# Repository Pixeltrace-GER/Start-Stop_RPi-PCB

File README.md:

> __Warning__  <br>**WORK IN PROGRESS** <br>Please wait for a stable release or get in touch with me.

# Start & Stop HAT PCB

## Features Raspberry
-  Cooling Fan 2510
-  GCode Button ~~5x~~ 3x
-  GCode Button Led ~~5x~~ 3x
-  Relay Connector for 2x 10A 250VAC

## Features D1mini
-  Start & Stop relay [HF46F/5-HS1]
-  I2C SSD1306 OLED
-  Error LED [red 0805]
-  WiFi-AP Config
-  EEPROM saved Config

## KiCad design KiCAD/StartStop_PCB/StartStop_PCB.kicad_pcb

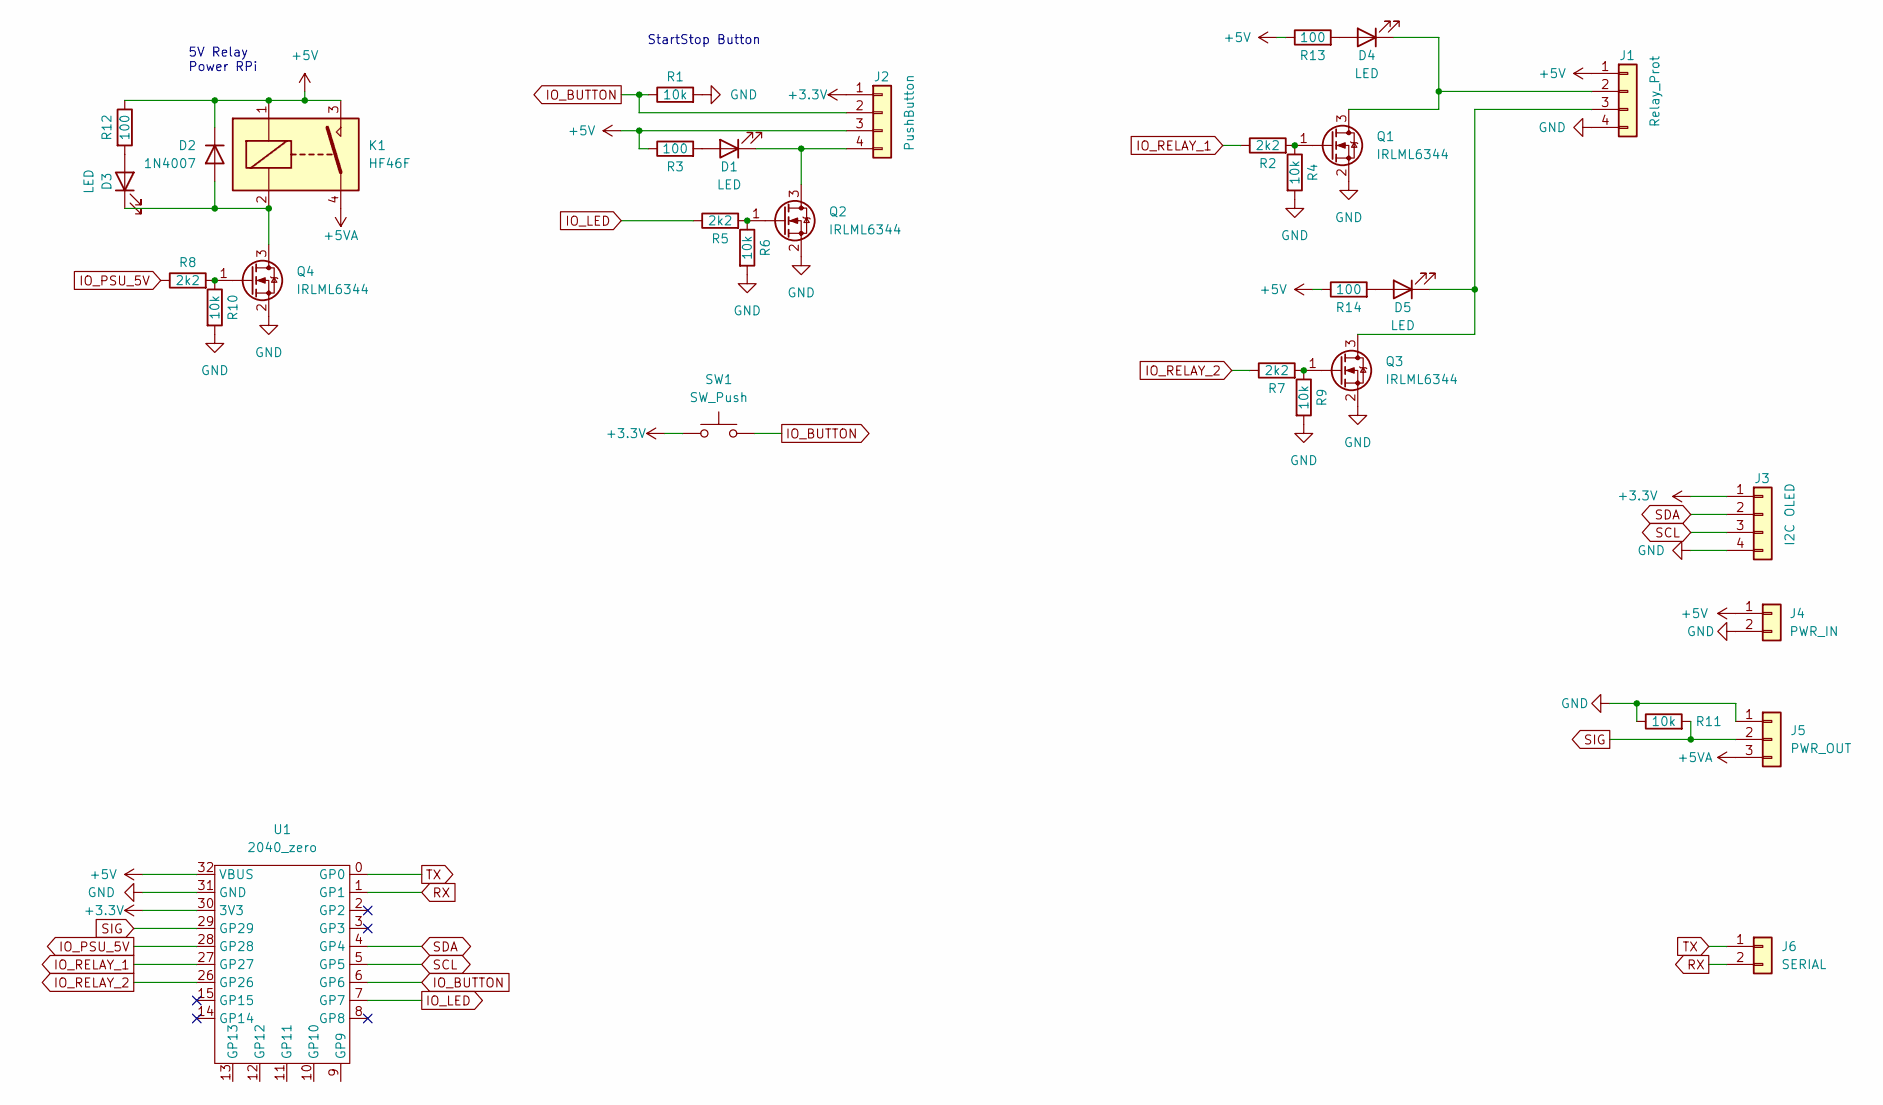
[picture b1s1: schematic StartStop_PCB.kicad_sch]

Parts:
D1, D3, D4, D5: LED; LED_0805_2012Metric
D2: 1N4007; D_SOD-123
J1: Relay_Prot; JST_XH_B4B-XH-A_1x04_P2.50mm_Vertical
J2: PushButton; JST_XH_B4B-XH-A_1x04_P2.50mm_Vertical
J3: I2C OLED; JST_XH_B4B-XH-A_1x04_P2.50mm_Vertical
J4: PWR_IN; Molex_Micro-Fit_3.0_43650-0215_1x02_P3.00mm_Vertical
J5: PWR_OUT; Molex_Micro-Fit_3.0_43650-0315_1x03_P3.00mm_Vertical
J6: SERIAL; JST_XH_B2B-XH-A_1x02_P2.50mm_Vertical
K1: HF46F
Q1, Q2, Q3, Q4: IRLML6344; SOT-23
R1, R4, R6, R9, R10, R11: 10k; R_0805_2012Metric
R2, R5, R7, R8: 2k2; R_0805_2012Metric
R3, R12, R13, R14: 100; R_0805_2012Metric
SW1: SW_Push; SW_04-03
U1: 2040_zero; rp2040_zero

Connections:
+3.3V: J2.1, J3.1, SW1.1, U1.30 (3V3)
+5V: D2.1 (K), J1.1, J2.3, J4.1, K1.1, K1.3, R3.1, R12.1, R13.1, R14.1, U1.32 (VBUS)
+5VA: J5.3, K1.4
GND: J1.4, J3.4, J4.2, J5.1, Q1.2 (S), Q2.2 (S), Q3.2 (S), Q4.2 (S), R1.2, R4.2, R6.2, R9.2, R10.2, R11.1, U1.31 (GND)
IO_BUTTON: J2.2, R1.1, SW1.2, U1.6 (GP6)
IO_LED: R5.1, U1.7 (GP7)
IO_PSU_5V: R8.1, U1.28 (GP28)
IO_RELAY_1: R2.1, U1.27 (GP27)
IO_RELAY_2: R7.1, U1.26 (GP26)
unnamed: D1.1 (K), J2.4, Q2.3 (D)
unnamed: D1.2 (A), R3.2
unnamed: D2.2 (A), D3.1 (K), K1.2, Q4.3 (D)
unnamed: D3.2 (A), R12.2
unnamed: D4.1 (K), J1.2, Q1.3 (D)
unnamed: D4.2 (A), R13.2
unnamed: D5.1 (K), J1.3, Q3.3 (D)
unnamed: D5.2 (A), R14.2
unnamed: Q1.1 (G), R2.2, R4.1
unnamed: Q2.1 (G), R5.2, R6.1
unnamed: Q3.1 (G), R7.2, R9.1
unnamed: Q4.1 (G), R8.2, R10.1
RX: J6.2, U1.1 (GP1)
SCL: J3.3, U1.5 (GP5)
SDA: J3.2, U1.4 (GP4)
SIG: J5.2, R11.2, U1.29 (GP29)
TX: J6.1, U1.0 (GP0)

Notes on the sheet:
5V Relay Power RPi
StartStop Button

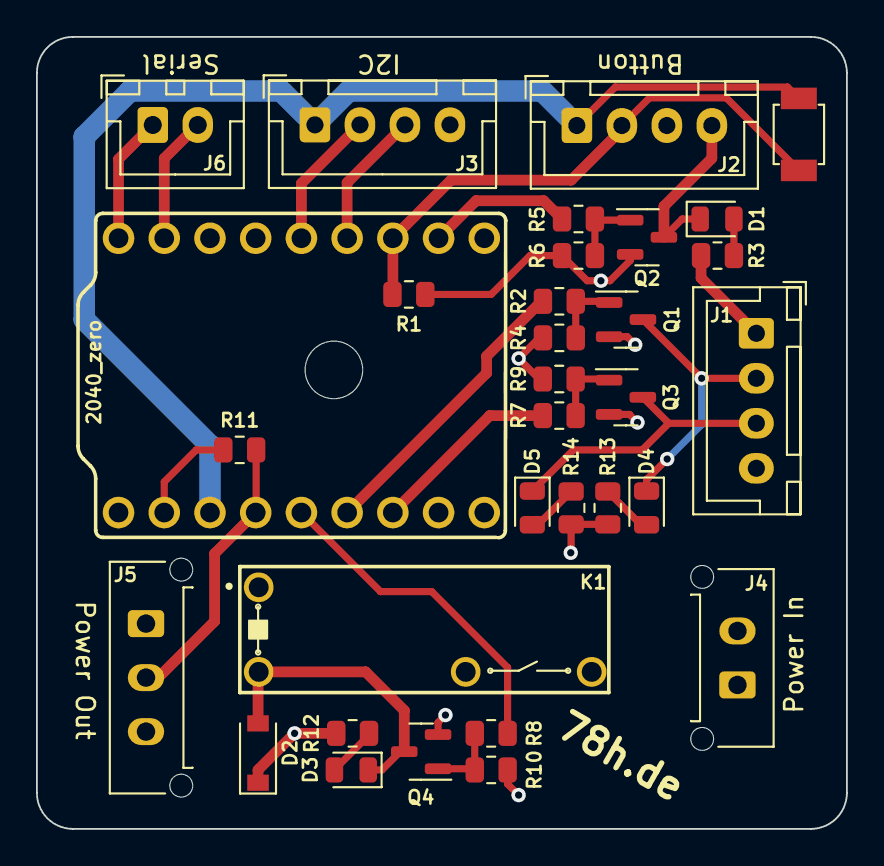
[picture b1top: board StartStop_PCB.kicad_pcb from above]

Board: 4 copper layers, 45.0 x 44.0 mm, 32 parts (0 on the bottom side), 26 nets.

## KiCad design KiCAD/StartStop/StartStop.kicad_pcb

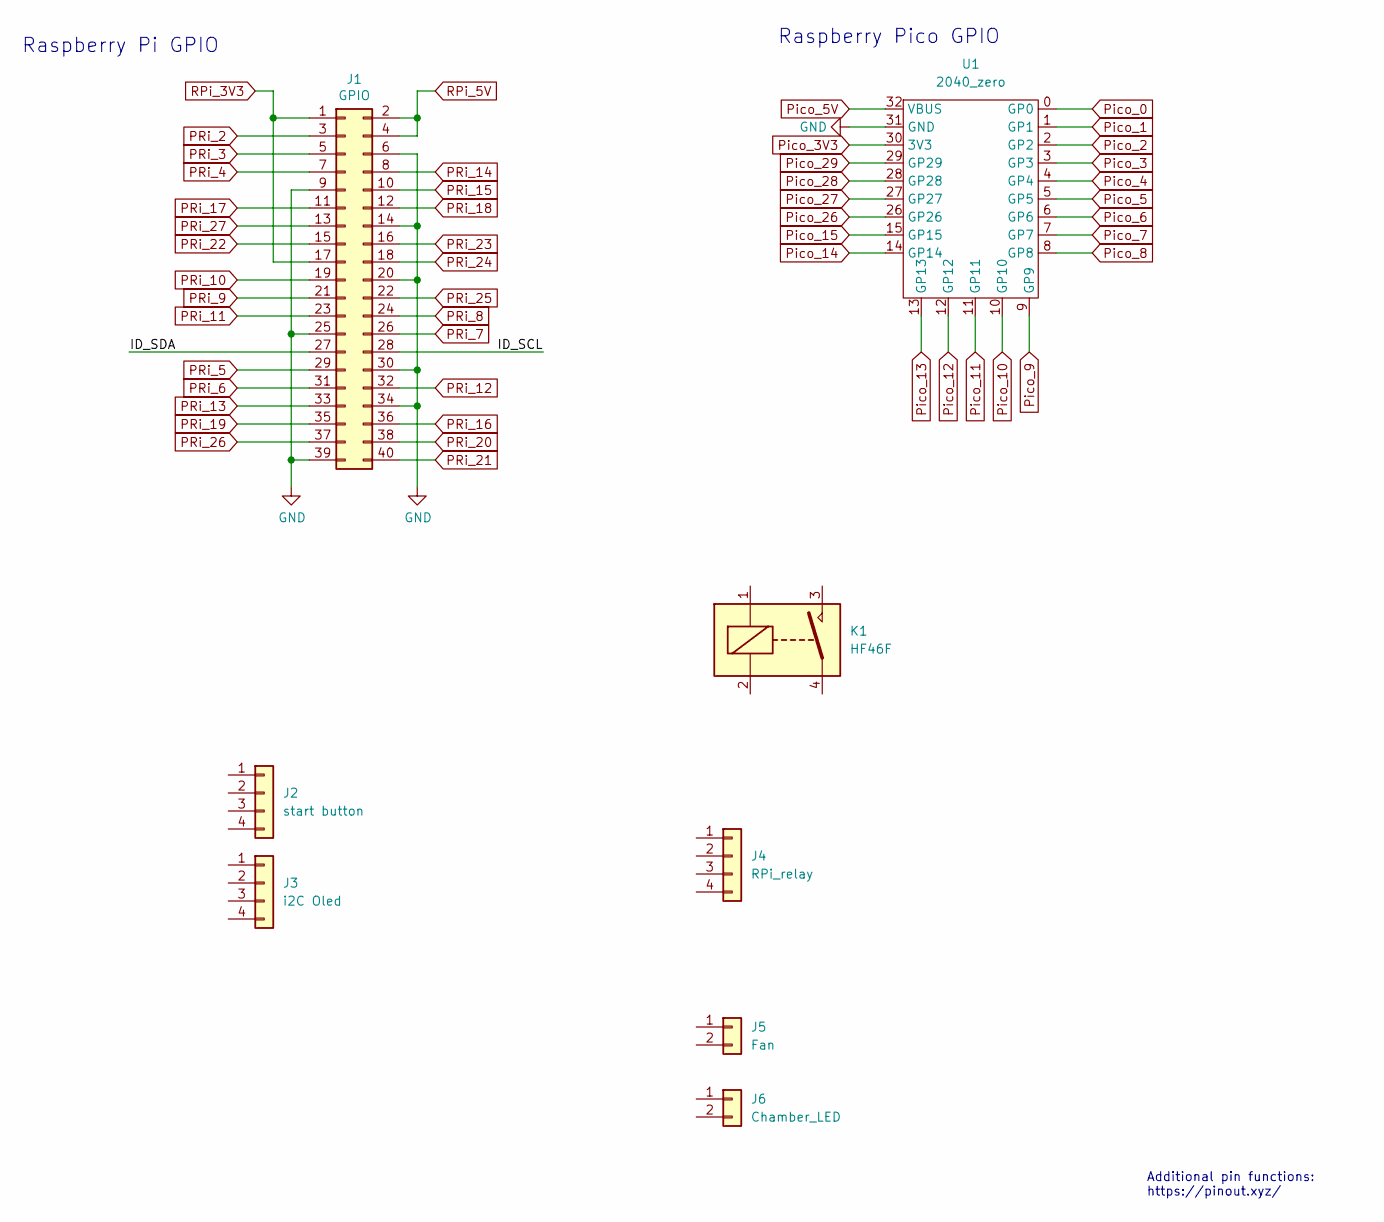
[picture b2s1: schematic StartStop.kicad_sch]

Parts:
J1: GPIO; PinSocket_2x20_P2.54mm_Vertical
J2: start button; JST_PH_B4B-PH-K_1x04_P2.00mm_Vertical
J3: i2C Oled; JST_PH_B4B-PH-K_1x04_P2.00mm_Vertical
J4: RPi_relay; JST_PH_B4B-PH-K_1x04_P2.00mm_Vertical
J5: Fan; JST_PH_B2B-PH-K_1x02_P2.00mm_Vertical
J6: Chamber_LED; JST_PH_B2B-PH-K_1x02_P2.00mm_Vertical
K1: HF46F
U1: 2040_zero; rp2040_zero

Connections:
/ID_SCL: J1.28
/ID_SDA: J1.27
GND: J1.6, J1.9, J1.14, J1.20, J1.25, J1.30, J1.34, J1.39, U1.31 (GND)
PRi_2: J1.3
PRi_3: J1.5
PRi_4: J1.7
PRi_5: J1.29
PRi_6: J1.31
PRi_7: J1.26
PRi_8: J1.24
PRi_9: J1.21
PRi_10: J1.19
PRi_11: J1.23
PRi_12: J1.32
PRi_13: J1.33
PRi_14: J1.8
PRi_15: J1.10
PRi_16: J1.36
PRi_17: J1.11
PRi_18: J1.12
PRi_19: J1.35
PRi_20: J1.38
PRi_21: J1.40
PRi_22: J1.15
PRi_23: J1.16
PRi_24: J1.18
PRi_25: J1.22
PRi_26: J1.37
PRi_27: J1.13
Pico_0: U1.0 (GP0)
Pico_1: U1.1 (GP1)
Pico_2: U1.2 (GP2)
Pico_3: U1.3 (GP3)
Pico_3V3: U1.30 (3V3)
Pico_4: U1.4 (GP4)
Pico_5: U1.5 (GP5)
Pico_5V: U1.32 (VBUS)
Pico_6: U1.6 (GP6)
Pico_7: U1.7 (GP7)
Pico_8: U1.8 (GP8)
Pico_9: U1.9 (GP9)
Pico_10: U1.10 (GP10)
Pico_11: U1.11 (GP11)
Pico_12: U1.12 (GP12)
Pico_13: U1.13 (GP13)
Pico_14: U1.14 (GP14)
Pico_15: U1.15 (GP15)
Pico_26: U1.26 (GP26)
Pico_27: U1.27 (GP27)
Pico_28: U1.28 (GP28)
Pico_29: U1.29 (GP29)
RPi_3V3: J1.1, J1.17
RPi_5V: J1.2, J1.4

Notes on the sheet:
Additional pin functions: https://pinout.xyz/
Raspberry Pi GPIO
Raspberry Pico GPIO

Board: 2 copper layers, 12 parts (1 on the bottom side), 3 nets, no tracks yet.

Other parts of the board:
MH1, MH2, MH3, MH4: MountingHole_2.7mm_M2.5

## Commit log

2022-09-14 add: Todo in README.md
2022-10-14 Init KiCAD
2022-12-11 Finish KiCAD
